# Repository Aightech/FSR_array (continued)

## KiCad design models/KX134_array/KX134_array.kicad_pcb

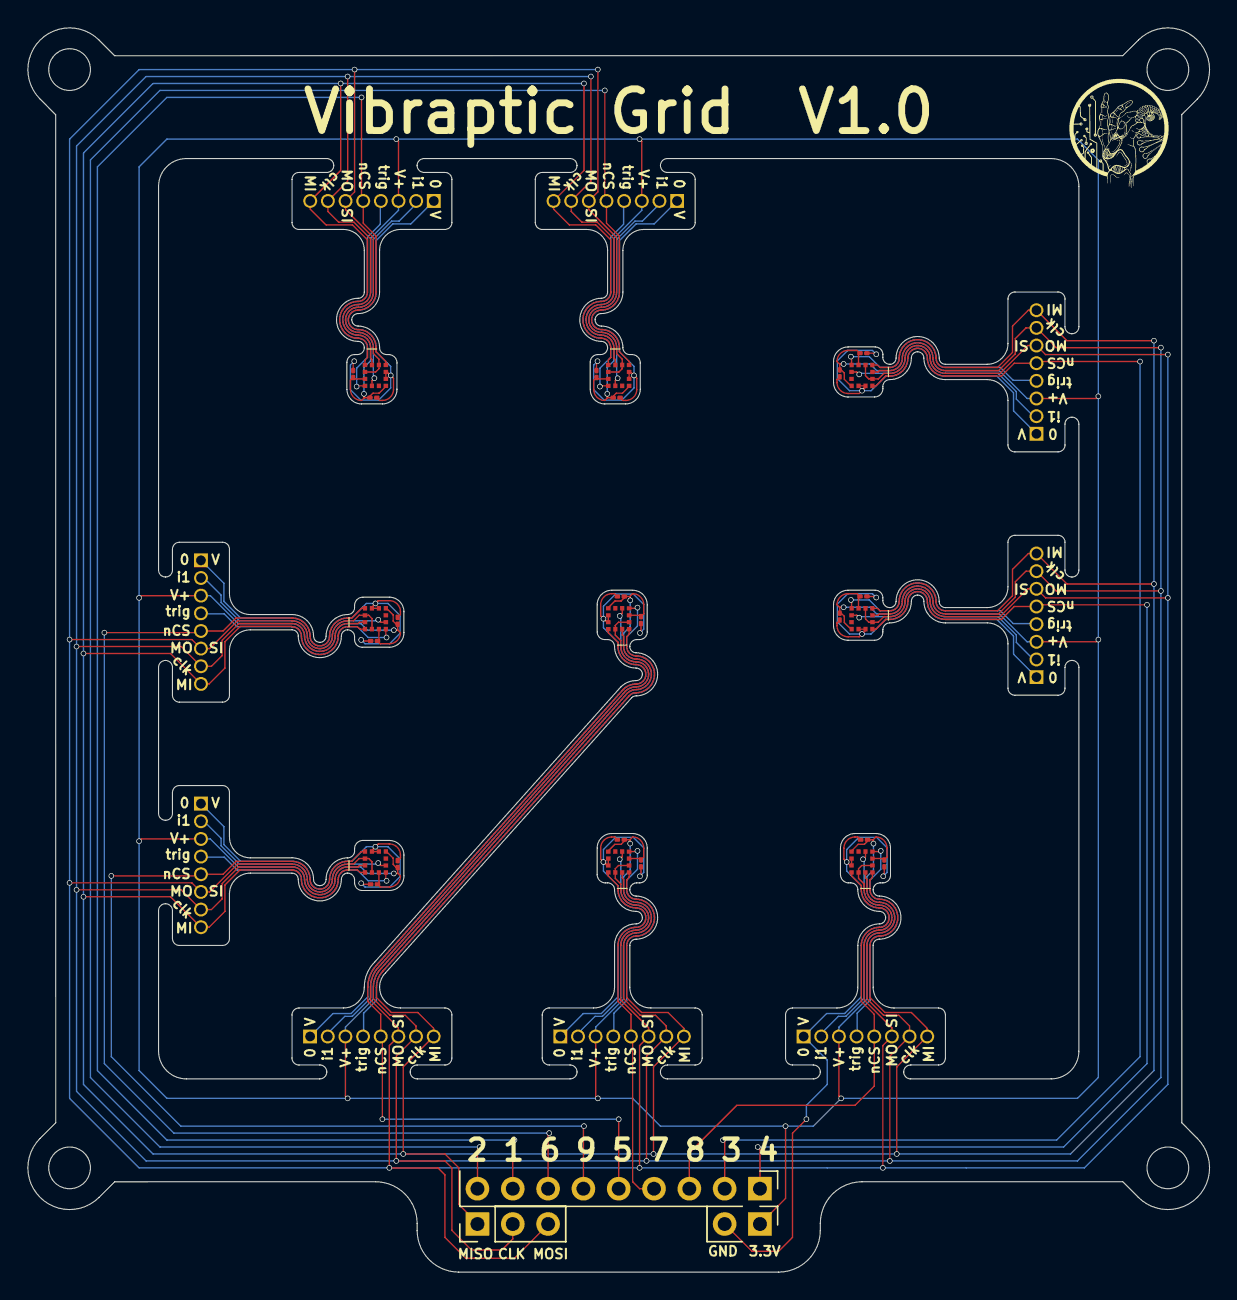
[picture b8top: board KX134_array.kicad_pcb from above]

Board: 2 copper layers, 85.0 x 89.5 mm, 39 parts (0 on the bottom side), 32 nets.

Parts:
C1, C3, C5, C7, C9, C11, C13, C15, C17: 100n; C_01005_0402Metric
C2, C4, C6, C8, C10, C12, C14, C16, C18: 1u; C_01005_0402Metric
J1, J2, J3, J4, J5, J6, J7, J8, J9: Conn_01x08_Socket; PinSocket_1x08_P1.27mm_Vertical
J10: Conn_01x09_Socket; PinHeader_1x09_P2.54mm_Vertical
J11: Conn_01x03_Socket; PinHeader_1x03_P2.54mm_Vertical
J12: Conn_01x02_Socket; PinHeader_1x02_P2.54mm_Vertical
U1, U2, U3, U4, U5, U6, U7, U8, U9: kx134; KX134-1211

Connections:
GND: C1.2, C2.1, C3.2, C4.1, C5.2, C6.1, C7.2, C8.1, C9.2, C10.1, C11.2, C12.1, C13.2, C14.1, C15.2, C16.1, C17.2, C18.1, J1.1, J2.1, J3.1, J4.1, J5.1, J6.1, J7.1, J8.1, J9.1, J12.2, U1.8 (GND), U1.9 (GND), U2.8 (GND), U2.9 (GND), U3.8 (GND), U3.9 (GND), U4.8 (GND), U4.9 (GND), U5.8 (GND), U5.9 (GND), U6.8 (GND), U6.9 (GND), U7.8 (GND), U7.9 (GND), U8.8 (GND), U8.9 (GND), U9.8 (GND), U9.9 (GND)
INT1_1: J1.2, U1.5 (INT1)
INT1_2: J2.2, U2.5 (INT1)
INT1_3: J3.2, U3.5 (INT1)
INT1_4: J4.2, U4.5 (INT1)
INT1_5: J5.2, U5.5 (INT1)
INT1_6: J6.2, U6.5 (INT1)
INT1_7: J7.2, U7.5 (INT1)
INT1_8: J8.2, U8.5 (INT1)
INT1_9: J9.2, U9.5 (INT1)
SDI: J1.6, J2.6, J3.6, J4.6, J5.6, J6.6, J7.6, J8.6, J9.6, J11.3, U1.2 (SDI/SDA), U1.11 (NC), U2.2 (SDI/SDA), U2.11 (NC), U3.2 (SDI/SDA), U3.11 (NC), U4.2 (SDI/SDA), U4.11 (NC), U5.2 (SDI/SDA), U5.11 (NC), U6.2 (SDI/SDA), U6.11 (NC), U7.2 (SDI/SDA), U7.11 (NC), U8.2 (SDI/SDA), U8.11 (NC), U9.2 (SDI/SDA), U9.11 (NC)
SDO: J1.8, J2.8, J3.8, J4.8, J5.8, J6.8, J7.8, J8.8, J9.8, J11.1, U1.1 (SDO/ADDR), U2.1 (SDO/ADDR), U3.1 (SDO/ADDR), U4.1 (SDO/ADDR), U5.1 (SDO/ADDR), U6.1 (SDO/ADDR), U7.1 (SDO/ADDR), U8.1 (SDO/ADDR), U9.1 (SDO/ADDR)
Sclk: J1.7, J2.7, J3.7, J4.7, J5.7, J6.7, J7.7, J8.7, J9.7, J11.2, U1.12 (SCLK/SCL), U2.12 (SCLK/SCL), U3.12 (SCLK/SCL), U4.12 (SCLK/SCL), U5.12 (SCLK/SCL), U6.12 (SCLK/SCL), U7.12 (SCLK/SCL), U8.12 (SCLK/SCL), U9.12 (SCLK/SCL)
TRIG_1: J1.4, U1.4 (TRIG)
TRIG_2: J2.4, U2.4 (TRIG)
TRIG_3: J3.4, U3.4 (TRIG)
TRIG_4: J4.4, U4.4 (TRIG)
TRIG_5: J5.4, U5.4 (TRIG)
TRIG_6: J6.4, U6.4 (TRIG)
TRIG_7: J7.4, U7.4 (TRIG)
TRIG_8: J8.4, U8.4 (TRIG)
TRIG_9: J9.4, U9.4 (TRIG)
VDD: C1.1, C2.2, C3.1, C4.2, C5.1, C6.2, C7.1, C8.2, C9.1, C10.2, C11.1, C12.2, C13.1, C14.2, C15.1, C16.2, C17.1, C18.2, J1.3, J2.3, J3.3, J4.3, J5.3, J6.3, J7.3, J8.3, J9.3, J12.1, U1.3 (IO_VDD), U1.7 (VDD), U2.3 (IO_VDD), U2.7 (VDD), U3.3 (IO_VDD), U3.7 (VDD), U4.3 (IO_VDD), U4.7 (VDD), U5.3 (IO_VDD), U5.7 (VDD), U6.3 (IO_VDD), U6.7 (VDD), U7.3 (IO_VDD), U7.7 (VDD), U8.3 (IO_VDD), U8.7 (VDD), U9.3 (IO_VDD), U9.7 (VDD)
nCS_1: J1.5, J10.8, U1.10 (nCS)
nCS_2: J2.5, J10.9, U2.10 (nCS)
nCS_3: J3.5, J10.2, U3.10 (nCS)
nCS_4: J4.5, J10.1, U4.10 (nCS)
nCS_5: J5.5, J10.5, U5.10 (nCS)
nCS_6: J6.5, J10.7, U6.10 (nCS)
nCS_7: J7.5, J10.4, U7.10 (nCS)
nCS_8: J8.5, J10.3, U8.10 (nCS)
nCS_9: J9.5, J10.6, U9.10 (nCS)

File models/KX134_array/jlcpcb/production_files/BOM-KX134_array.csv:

Comment,Designator,Footprint,LCSC
Conn_01x08_Socket,J7,PinSocket_1x08_P1.27mm_Vertical,
Conn_01x08_Socket,J1,PinSocket_1x08_P1.27mm_Vertical,
Conn_01x08_Socket,J2,PinSocket_1x08_P1.27mm_Vertical,
Conn_01x08_Socket,J8,PinSocket_1x08_P1.27mm_Vertical,
Conn_01x08_Socket,J3,PinSocket_1x08_P1.27mm_Vertical,
Conn_01x08_Socket,J9,PinSocket_1x08_P1.27mm_Vertical,
Conn_01x08_Socket,J4,PinSocket_1x08_P1.27mm_Vertical,
Conn_01x08_Socket,J5,PinSocket_1x08_P1.27mm_Vertical,
Conn_01x08_Socket,J6,PinSocket_1x08_P1.27mm_Vertical,
1u,C10,C_01005_0402Metric,
1u,C2,C_01005_0402Metric,
Conn_01x09_Socket,J10,PinHeader_1x09_P2.54mm_Vertical,
100n,C9,C_01005_0402Metric,
100n,C7,C_01005_0402Metric,
100n,C15,C_01005_0402Metric,
100n,C17,C_01005_0402Metric,
1u,C12,C_01005_0402Metric,
1u,C8,C_01005_0402Metric,
kx134,U5,KX134-1211,
kx134,U3,KX134-1211,
kx134,U9,KX134-1211,
kx134,U1,KX134-1211,
kx134,U8,KX134-1211,
100n,C1,C_01005_0402Metric,
kx134,U6,KX134-1211,
1u,C14,C_01005_0402Metric,
100n,C11,C_01005_0402Metric,
Conn_01x02_Socket,J12,PinHeader_1x02_P2.54mm_Vertical,
1u,C16,C_01005_0402Metric,
100n,C5,C_01005_0402Metric,
1u,C4,C_01005_0402Metric,
kx134,U2,KX134-1211,
Conn_01x03_Socket,J11,PinHeader_1x03_P2.54mm_Vertical,
1u,C6,C_01005_0402Metric,
kx134,U4,KX134-1211,
kx134,U7,KX134-1211,
1u,C18,C_01005_0402Metric,
100n,C3,C_01005_0402Metric,
100n,C13,C_01005_0402Metric,

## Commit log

2022-07-01 added board
2022-07-01 added datasheets
2022-07-01 Solidwork model
2022-08-29 added matlab script
2022-08-29 updated the python script to record with timestamps
2022-08-29 fixed closing issue of the serial port in the record.py script
2022-08-29 n can be set via command arg
2022-08-31 letters models
2022-09-13 big_letters
2022-09-14 update big letters
2022-09-14 update on letters
2022-10-25 v3 kicad
2022-11-11 v2 pcbboard and comments on matlab script
2023-05-25 working step for the cpp lsl publisher
2023-05-28 Create FSR support
2023-07-17 fixed minor bug + added ethernet teensy code
2023-08-14 updated LIS3DH array
2024-03-16 updated lis3dh array: fpc connectors
2024-07-18 added LIS2DH version with or gate to solve SPI/i2C interaction
2024-07-20 working code for the accelerometers + FSRs
2024-08-31 added or gate on each acc to prevent I2C interference when the chip have CSB high
2024-09-01 updated lis2dh arrays
2024-09-29 new custom fsr model
2024-10-04 modify the fixation position to fit better on finger
2024-10-21 added teeardrops
2024-10-23 added scripts for customFSR
2025-02-27 starting tear drops
